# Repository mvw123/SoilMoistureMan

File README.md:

Soil Moisture Man [WIP]
===============

WARNING: THIS PROJECT WILL CAUSE ELECTROLYSIS AND SO THE PLATING ON THE LEGS WILL DEGRADE OVER TIME. SOME CONTAMINATION OF THE SOIL WILL OCCUR. DO NOT USE ON EDIBLE PLANTS. 

The Soil moisture man CAD files are drawn using Eagle CAD free edition. 
Simulation files are included. These use Simetrix (windows only) http://www.simetrix.co.uk/site/index.html

The Soil Moisture Man is an educational "open source hardware" project which flashes warning LEDs when your plants soil becomes dry. 
This stops you under-watering and killing your plants. 
* The device uses standard electronic circuits to measure the resistance of the soil. 
* Transistors and variable resistor test the soil moisture level and switch the circuit on when required
* An Astable multivibrator is used to flash the LEDs at a certain frequency and duty cycle. 
* This is NOT a commercial product and is not suitable for commercial sale. It is to be used solely for educational use. We (i) do not warrant its use in any way shape or form. 

To use the soil moisture man, you need to calibrate the device to flash its LEDs when your soil becomes dry to the point where it will need watering. 
You do this by :- 
* Select a plant whose soil has just reached the point where it needs watering, but where the soil is not dry or parched.
* Insert the gold coloured legs into the soil next to a plant, up to the point where the gold flashing on the legs stops. Inserting the device further could damage the circuitry.
* IMPORTANT: Press the soil firmly against the legs, so that it makes good contact. Failing to do this will cause the LEDs to flash in error.
* Turn VR1 until the LEDs just start to flash consistently. 
* Note that different types of soil have different resistances. If you have a multimeter, its interesting to do take some measurements in different soil types. This project is setup for house plants which usually use a fine soil which has a lower resistance than the soil you would normally find in your back garden. 

CAD C [WIP]
===========

CAD C is being updated due to some minor issues on CAD B which have been raised in github.
Battery lifetime is being tested. 

CAD B [TESTED - Some issues present] 
=====

Changed the circuit around from CAD A. 
The Astable multivibrator is now turned on by the soil moisture sensor transistor. 
This saves some small amounts of power and thus increases the battery life.
BOM parts updated and new VR1 chosen

CAD A [FAULTY] 
=====

Initial schematic release.
Ignore this version, it has been superseded by CAD B
Released to OSH park with a bug. 
The ground track was missing on the VR1 trimmer
The CAM file output did not work correctly due to the solder mask resist keep out area size. it needed pulling back from the edge of the PCB.
Final component selection was not completed and has now changed on CAD B. 
The circuit design changed on CAD B.

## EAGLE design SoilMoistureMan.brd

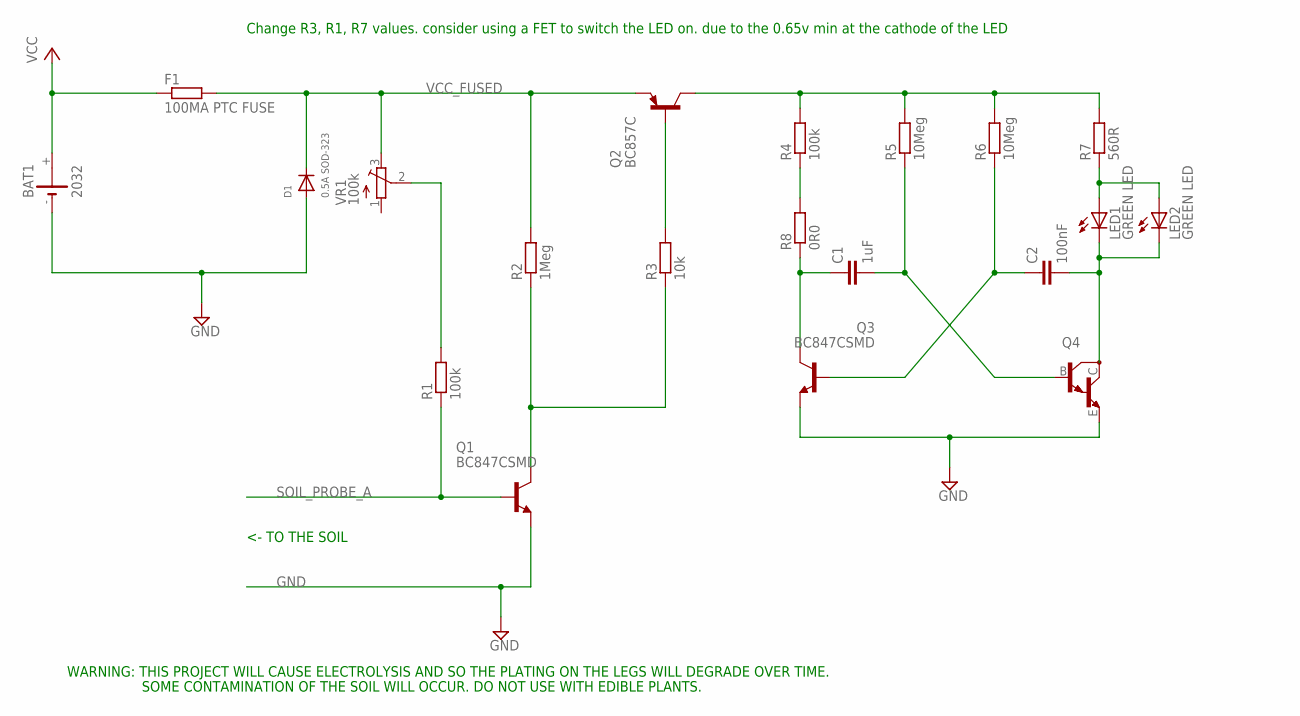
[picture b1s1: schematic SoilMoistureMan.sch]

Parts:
BAT1: 2032; KZH20SMD; MPN SMTU 2032-LF
C1: 1uF; C0603; MPN C1608X5R1C105K080AA
C2: 100nF; C0603; MPN MC0603B104K160CT
D1: 0.5A SOD-323; SOD-323F; MPN PMEG3010EJ,115
F1: 100MA PTC FUSE; R0805; MPN MF-PSMF010X-2
LED1, LED2: GREEN LED; P-LCC-2; MPN LGT67K-H2K1-24-Z
Q1, Q3: BC847CSMD; SOT23; MPN BC847C-7-F
Q2: BC857C; SOT23-BEC; MPN BC857C-7-F
Q4: MMBTA13LT1; SOT23-BEC; MPN BCV27
R1, R4: 100k; R0603; MPN CRGH0603J100K
R2: 1Meg; R0603; MPN CRGH0603J1M0
R3: 10k; R0603; MPN CR0603-JW-103GLF
R5, R6: 10Meg; R0603; MPN MC0063W0603110M0
R7: 560R; R0603; MPN CRGH0603J560R
R8: 0R0; R0603; MPN MC0603SAF0000T5E
VR1: 100k; TC33X; MPN TS53YJ104MR10

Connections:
GND: BAT1.-, D1.A, Q1.2 (E), Q3.2 (E), Q4.E
unnamed: Q2.C, R4.2, R5.2, R6.2, R7.2
unnamed: R4.1, R8.2
unnamed: Q2.B, R3.2
unnamed: LED1.A, LED2.A, R7.1
unnamed: C1.1, Q3.3 (C), R8.1
unnamed: R1.2, VR1.2 (S)
unnamed: C2.1, Q3.1 (B), R6.1
unnamed: C2.2, LED1.C, LED2.C, Q4.C
unnamed: C1.2, Q4.B, R5.1
unnamed: Q1.3 (C), R2.1, R3.1
SOIL_PROBE_A: Q1.1 (B), R1.1
VCC: BAT1.+, F1.1
VCC_FUSED: D1.C, F1.2, Q2.E, R2.2, VR1.3 (E)

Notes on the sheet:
<- TO THE SOIL
SOME CONTAMINATION OF THE SOIL WILL OCCUR. DO NOT USE WITH EDIBLE PLANTS.
WARNING: THIS PROJECT WILL CAUSE ELECTROLYSIS AND SO THE PLATING ON THE LEGS WILL DEGRADE OVER TIME.
Change R3, R1, R7 values. consider using a FET to switch the LED on. due to the 0.65v min at the cathode of the LED

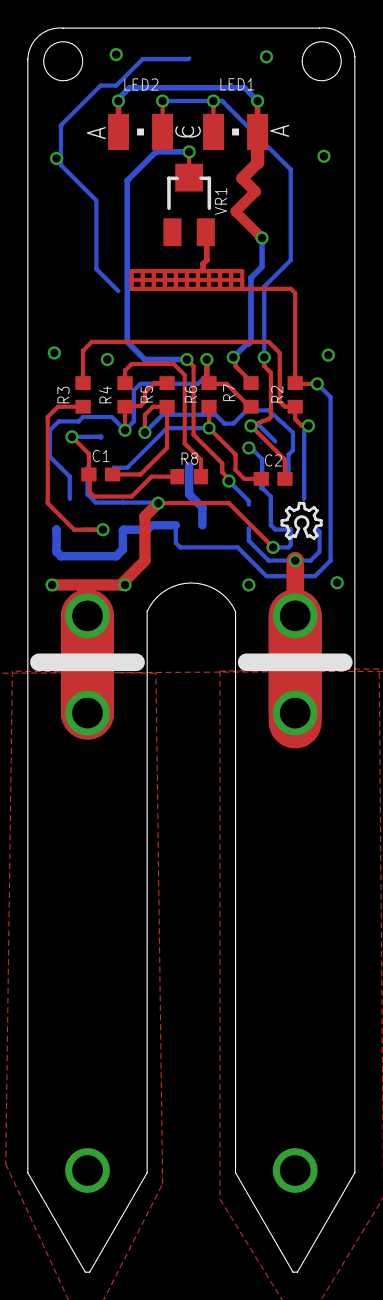
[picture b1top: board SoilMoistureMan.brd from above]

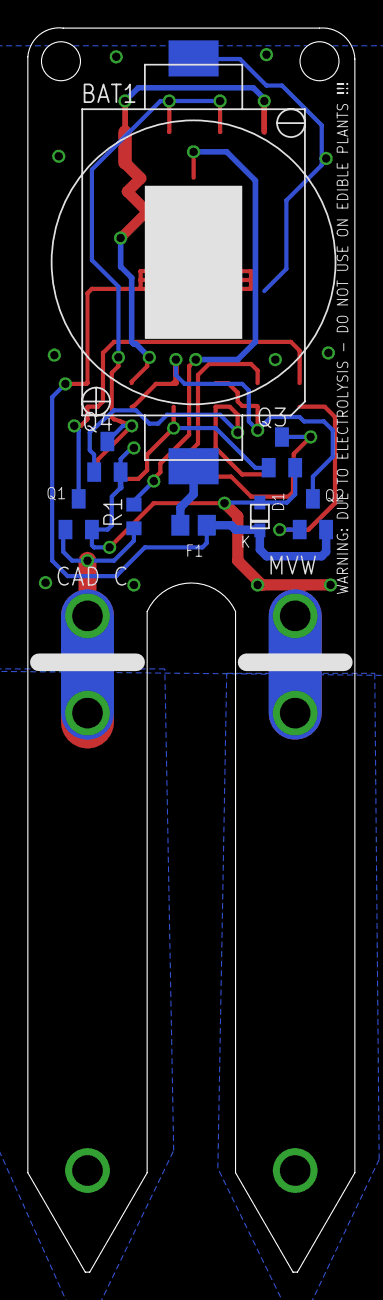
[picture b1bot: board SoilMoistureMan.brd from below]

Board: 2 copper layers, 23.5 x 89.4 mm, 21 parts (8 on the bottom side), 14 nets.

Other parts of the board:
U$1: OSHW_8X100_NOTEXT

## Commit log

2014-05-02 First commit for WIP CAD B of soil moisture man
    First commit for WIP CAD B of soil moisture man
    CAD A is archived in the zip file. But CAD A won’t work due to missing
    a ground connection on the VR1 trimmer
2014-05-02 name corrections
2014-05-02 Added simulation files to the repo
    Added simulation files to the repo
    The simulations need more work to prove they do what they are supposed
    to do.
2014-05-02 added comment regarding simetrix files
2014-05-02 adding extra components
    started adding extra components to ensure circuitry works
2014-05-05 schematic and Routing changes
    schematic and Routing changes still WIP
2014-05-05 UpdatedSimtoLatestSchematic
    UpdatedSimtoLatestSchematic
2014-05-07 Layout changes and Bat 2 changed to bat 1
2014-05-10 Commit PDF
2014-10-02 CAD B Commit
    CAD B Commit - used to produce CAD B boards
2014-10-12 First CAD C commit
    Updated one resistor value from 1MOhm to 100k. added warning text about
    electrolysis to pcb and another to the schematic
2014-10-12 minor test amendments
2014-11-24 Improved usage notes.
    Improved usage notes.
2014-11-24 Committing latest updates on CAD C
    Committing latest updates on CAD C
2014-12-21 committing latest updates
    committing latest updates
2014-12-31 No Known changes
    No Known changes
2015-02-15 latest commit
2016-02-28 Added pdf of schematic
    Added pdf of schematic
2017-09-25 ds store update
